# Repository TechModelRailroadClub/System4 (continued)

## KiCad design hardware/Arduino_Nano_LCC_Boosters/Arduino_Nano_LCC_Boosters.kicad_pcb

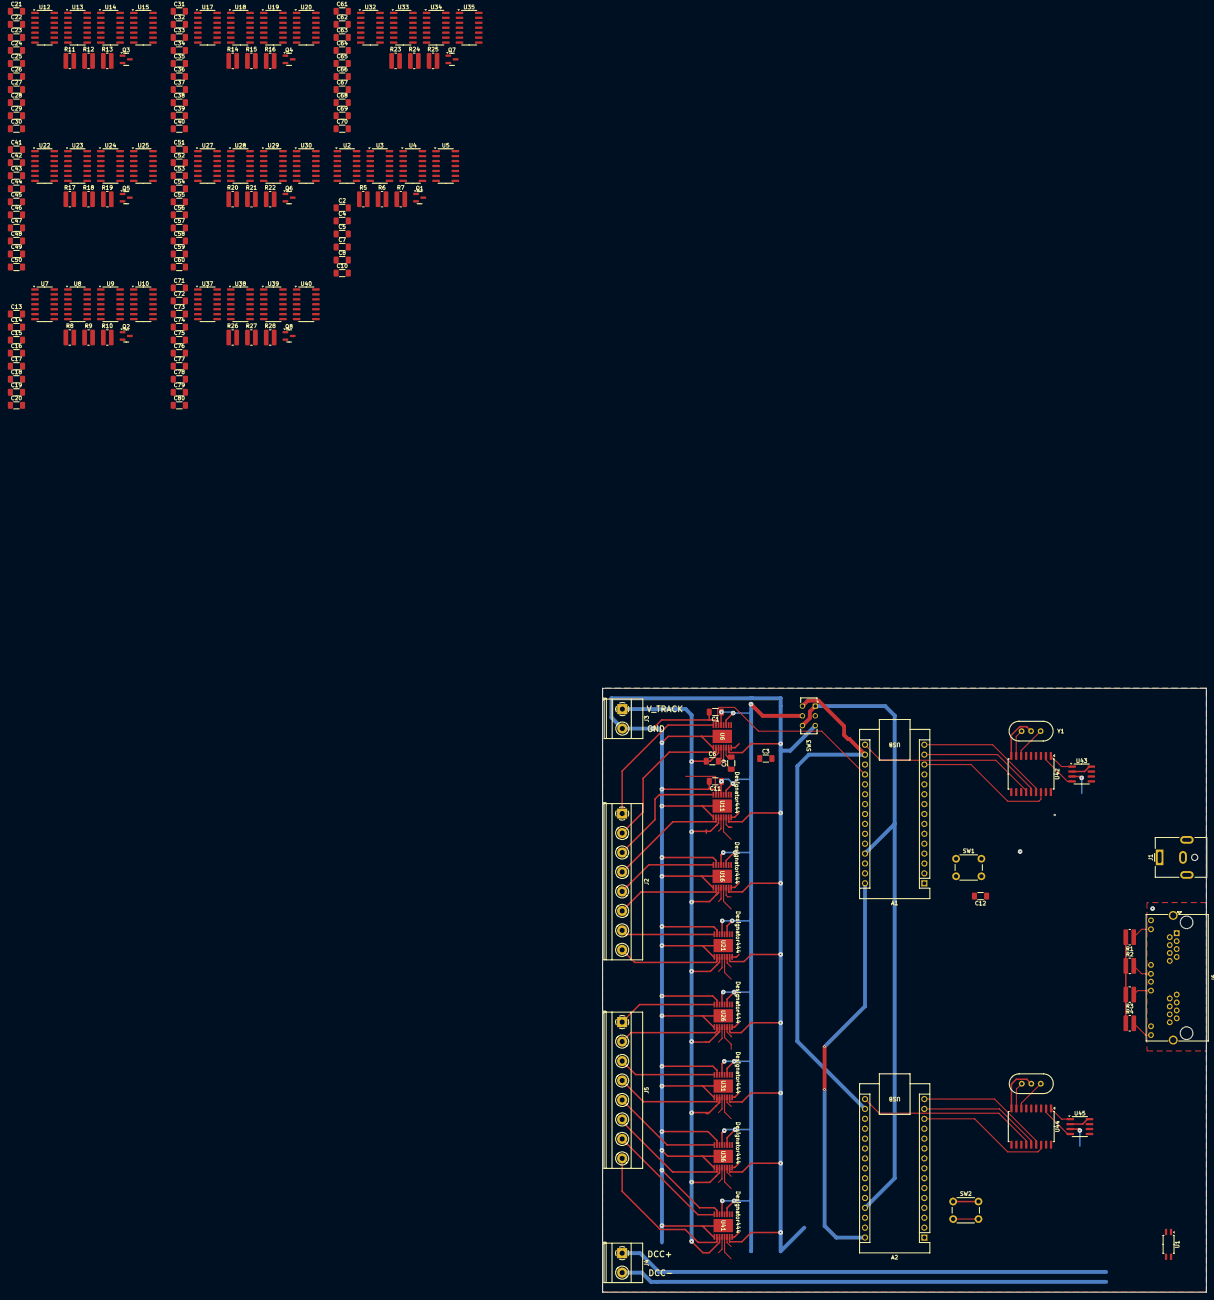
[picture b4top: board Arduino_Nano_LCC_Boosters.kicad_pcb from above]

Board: 2 copper layers, 155.0 x 155.0 mm, 174 parts (0 on the bottom side), 215 nets.

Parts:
A1, A2: Arduino_Nano_v3.x; Arduino_Nano
C1, C2, C3, C4, C5, C6, C8, C11, C12, C13, C14, C15, C16, C18, C21, C22, C23, C24, C25, C26, C28, C31, C32, C33, C34, C35, C36, C38, C41, C42, C43, C44, C45, C46, C48, C51, C52, C53, C54, C55, C56, C58, C61, C62, C63, C64, C65, C66, C68, C71, C72, C73, C74, C75, C76, C78: C100n; C_1206_3216Metric_Pad1.33x1.80mm_HandSolder
C7, C17, C27, C37, C47, C57, C67, C77: C10u; C_1206_3216Metric_Pad1.33x1.80mm_HandSolder
C9, C10, C19, C20, C29, C30, C39, C40, C49, C50, C59, C60, C69, C70, C79, C80: C22n; C_1206_3216Metric_Pad1.33x1.80mm_HandSolder
J1: Barrel_Jack_MountingPin; BarrelJack_CUI_PJ-063AH_Horizontal
J2, J5: Screw_Terminal_01x08; TerminalBlock_Phoenix_MKDS-1,5-8_1x08_P5.00mm_Horizontal
J3, J4: Screw_Terminal_01x02; TerminalBlock_Phoenix_MKDS-1,5-2_1x02_P5.00mm_Horizontal
J6: RJ45_LED_Shielded_x2; RJ45_Amphenol_RJHSE538X-02
Q1, Q2, Q3, Q4, Q5, Q6, Q7, Q8: AO3400A; SOT-23
R1, R2, R3, R4: R1k; R_0815_2038Metric_Pad1.20x4.05mm_HandSolder
R5, R8, R11, R14, R17, R20, R23, R26: R47k; R_0815_2038Metric_Pad1.20x4.05mm_HandSolder
R6, R9, R12, R15, R18, R21, R24, R27: R1k43; R_0815_2038Metric_Pad1.20x4.05mm_HandSolder
R7, R10, R13, R16, R19, R22, R25, R28: R732; R_0815_2038Metric_Pad1.20x4.05mm_HandSolder
SW1, SW2: SW_Push; SW_PUSH_6mm_H4.3mm
SW3: SW_Slide_DPDT; SW_CK_JS202011CQN_DPDT_Straight
U1: ACPL-214-500E; SOP-4_4.4x2.6mm_P1.27mm
U2, U3, U4, U5, U7, U8, U9, U10, U12, U13, U14, U15, U17, U18, U19, U20, U22, U23, U24, U25, U27, U28, U29, U30, U32, U33, U34, U35, U37, U38, U39, U40: 7410; SOIC-14_3.9x8.7mm_P1.27mm
U6, U11, U16, U21, U26, U31, U36, U41: DRV8874PWPR; PWP0016J_NV
U42, U44: MCP2515-xSO; SOIC-18W_7.5x11.6mm_P1.27mm
U43, U45: MCP2562-E-SN; SOIC-8_3.9x4.9mm_P1.27mm
Y1, Y2: 16.0 MHz, 22pF; Crystal_HC49-U-3Pin_Vertical

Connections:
3v3_IOREF: Q1.1 (G), Q2.1 (G), Q3.1 (G), Q4.1 (G), Q5.1 (G), Q6.1 (G), Q7.1 (G), Q8.1 (G), SW3.2 (B)
+3.3V: A1.17 (3V3), A2.17 (3V3), SW3.6 (C)
+5V: A1.27 (+5V), A2.27 (+5V), SW3.1 (A), SW3.4 (A), U43.3 (VDD), U45.3 (VDD)
/can_h: J6.1, J6.13, U43.7 (CANH), U45.7 (CANH)
/can_l: J6.2, J6.14, U43.6 (CANL), U45.6 (CANL)
/can_shield: J6.6, J6.18, J6.SH
/cipo_1: A1.15 (D12), U42.15 (SO)
/cipo_2: A2.15 (D12), U44.15 (SO)
/copi_1: A1.14 (D11), U42.14 (SI)
/copi_2: A2.14 (D11), U44.14 (SI)
/cs_1: A1.13 (D10), U42.16 (~CS)
/cs_2: A2.13 (D10), U44.16 (~CS)
/dcc_en_A: A1.25 (A6), U2.1, U2.2, U2.13, U3.2, U3.4, U4.2, U4.4
/dcc_en_B: A1.26 (A7), U7.1, U7.2, U7.13, U8.2, U8.4, U9.2, U9.4
/dcc_en_C: A1.2 (D0/RX), U12.1, U12.2, U12.13, U13.2, U13.4, U14.2, U14.4
/dcc_en_D: A1.1 (D1/TX), U17.1, U17.2, U17.13, U18.2, U18.4, U19.2, U19.4
/dcc_en_E: A2.25 (A6), U22.1, U22.2, U22.13, U23.2, U23.4, U24.2, U24.4
/dcc_en_F: A2.26 (A7), U27.1, U27.2, U27.13, U28.2, U28.4, U29.2, U29.4
/dcc_en_G: A2.2 (D0/RX), U32.1, U32.2, U32.13, U33.2, U33.4, U34.2, U34.4
/dcc_en_H: A2.1 (D1/TX), U37.1, U37.2, U37.13, U38.2, U38.4, U39.2, U39.4
/dcc_p: A1.11 (D8), A2.11 (D8), U1.3, U2.9, U2.10, U2.11, U3.3, U4.1, U7.9, U7.10, U7.11, U8.3, U9.1, U12.9, U12.10, U12.11, U13.3, U14.1, U17.9, U17.10, U17.11, U18.3, U19.1, U22.9, U22.10, U22.11, U23.3, U24.1, U27.9, U27.10, U27.11, U28.3, U29.1, U32.9, U32.10, U32.11, U33.3, U34.1, U37.9, U37.10, U37.11, U38.3, U39.1
/dir_A: A1.23 (A4), U2.3, U2.4, U2.5, U3.13, U4.11, U4.13
/dir_B: A1.24 (A5), U7.3, U7.4, U7.5, U8.13, U9.11, U9.13
/dir_C: A1.5 (D2), U12.3, U12.4, U12.5, U13.13, U14.11, U14.13
/dir_D: A1.7 (D4), U17.3, U17.4, U17.5, U18.13, U19.11, U19.13
/dir_E: A2.23 (A4), U22.3, U22.4, U22.5, U23.13, U24.11, U24.13
/dir_F: A2.24 (A5), U27.3, U27.4, U27.5, U28.13, U29.11, U29.13
/dir_G: A2.5 (D2), U32.3, U32.4, U32.5, U33.13, U34.11, U34.13
/dir_H: A2.7 (D4), U37.3, U37.4, U37.5, U38.13, U39.11, U39.13
/out1_A: J2.1, U6.8 (OUT1)
/out1_B: J2.3, U11.8 (OUT1)
/out1_C: J2.5, U16.8 (OUT1)
/out1_D: J2.7, U21.8 (OUT1)
/out1_E: J5.1, U26.8 (OUT1)
/out1_F: J5.3, U31.8 (OUT1)
/out1_G: J5.5, U36.8 (OUT1)
/out1_H: J5.7, U41.8 (OUT1)
/out2_A: J2.2, U6.10 (OUT2)
/out2_B: J2.4, U11.10 (OUT2)
/out2_C: J2.6, U16.10 (OUT2)
/out2_D: J2.8, U21.10 (OUT2)
/out2_E: J5.2, U26.10 (OUT2)
/out2_F: J5.4, U31.10 (OUT2)
/out2_G: J5.6, U36.10 (OUT2)
/out2_H: J5.8, U41.10 (OUT2)
/pwm_A: A1.6 (D3), U3.9, U4.9
/pwm_B: A1.12 (D9), U8.9, U9.9
/pwm_C: A1.9 (D6), U13.9, U14.9
/pwm_D: A1.8 (D5), U18.9, U19.9
/pwm_E: A2.6 (D3), U23.9, U24.9
/pwm_F: A2.12 (D9), U28.9, U29.9
/pwm_G: A2.9 (D6), U33.9, U34.9
/pwm_H: A2.8 (D5), U38.9, U39.9
/pwr_n: J6.7, J6.19
/pwr_p: J6.8, J6.20
/raw_dcc_n: J4.2, J6.4, J6.16
/raw_dcc_p: J4.1, J6.5, J6.17, U1.1
/sck_1: A1.16 (D13), U42.13 (SCK)
/sck_2: A2.16 (D13), U44.13 (SCK)
/sense_A: A1.19 (A0), C10.1, R6.1, U6.6 (IPROPI)
/sense_B: A1.20 (A1), C20.1, R9.1, U11.6 (IPROPI)
/sense_C: A1.21 (A2), C30.1, R12.1, U16.6 (IPROPI)
/sense_D: A1.22 (A3), C40.1, R15.1, U21.6 (IPROPI)
/sense_E: A2.19 (A0), C50.1, R18.1, U26.6 (IPROPI)
/sense_F: A2.20 (A1), C60.1, R21.1, U31.6 (IPROPI)
/sense_G: A2.21 (A2), C70.1, R24.1, U36.6 (IPROPI)
/sense_H: A2.22 (A3), C80.1, R27.1, U41.6 (IPROPI)
/~led_1: A1.10 (D7), J6.9, J6.21
/~led_2: A2.10 (D7), J6.11, J6.23
/~reset_1: A1.3 (~RESET), A1.28 (~RESET), SW1.2, U42.17 (~RESET)
/~reset_2: A2.3 (~RESET), A2.28 (~RESET), SW2.2, U44.17 (~RESET)
GND: A1.4 (GND), A1.29 (GND), A2.4 (GND), A2.29 (GND), C1.2, C2.2, C3.2, C4.2, C5.2, C7.2, C8.2, C10.2, C11.2, C13.2, C14.2, C15.2, C17.2, C18.2, C20.2, C21.2, C22.2, C23.2, C24.2, C25.2, C27.2, C28.2, C30.2, C31.2, C32.2, C33.2, C34.2, C35.2, C37.2, C38.2, C40.2, C41.2, C42.2, C43.2, C44.2, C45.2, C47.2, C48.2, C50.2, C51.2, C52.2, C53.2, C54.2, C55.2, C57.2, C58.2, C60.2, C61.2, C62.2, C63.2, C64.2, C65.2, C67.2, C68.2, C70.2, C71.2, C72.2, C73.2, C74.2, C75.2, C77.2, C78.2, C80.2, J1.2, J1.MP (MountPin), J3.2, J6.3, J6.15, Q1.2 (S), Q2.2 (S), Q3.2 (S), Q4.2 (S), Q5.2 (S), Q6.2 (S), Q7.2 (S), Q8.2 (S), R7.2, R10.2, R13.2, R16.2, R19.2, R22.2, R25.2, R28.2, SW1.1, SW2.1, SW3.3 (C), U1.2, U2.7 (GND), U3.7 (GND), U4.7 (GND), U5.7 (GND), U6.7 (IMODE), U6.9 (PGND), U6.15 (GND), U6.17 (PAD), U7.7 (GND), U8.7 (GND), U9.7 (GND), U10.7 (GND), U11.7 (IMODE), U11.9 (PGND), U11.15 (GND), U11.17 (PAD), U12.7 (GND), U13.7 (GND), U14.7 (GND), U15.7 (GND), U16.7 (IMODE), U16.9 (PGND), U16.15 (GND), U16.17 (PAD), U17.7 (GND), U18.7 (GND), U19.7 (GND), U20.7 (GND), U21.7 (IMODE), U21.9 (PGND), U21.15 (GND), U21.17 (PAD), U22.7 (GND), U23.7 (GND), U24.7 (GND), U25.7 (GND), U26.7 (IMODE), U26.9 (PGND), U26.15 (GND), U26.17 (PAD), U27.7 (GND), U28.7 (GND), U29.7 (GND), U30.7 (GND), U31.7 (IMODE), U31.9 (PGND), U31.15 (GND), U31.17 (PAD), U32.7 (GND), U33.7 (GND), U34.7 (GND), U35.7 (GND), U36.7 (IMODE), U36.9 (PGND), U36.15 (GND), U36.17 (PAD), U37.7 (GND), U38.7 (GND), U39.7 (GND), U40.7 (GND), U41.7 (IMODE), U41.9 (PGND), U41.15 (GND), U41.17 (PAD), U42.9 (VSS), U43.2 (VSS), U43.8 (STBY), U44.9 (VSS), U45.2 (VSS), U45.8 (STBY), Y1.2, Y2.2
IOREF: C1.1, C2.1, C3.1, C4.1, C5.1, C11.1, C13.1, C14.1, C15.1, C21.1, C22.1, C23.1, C24.1, C25.1, C31.1, C32.1, C33.1, C34.1, C35.1, C41.1, C42.1, C43.1, C44.1, C45.1, C51.1, C52.1, C53.1, C54.1, C55.1, C61.1, C62.1, C63.1, C64.1, C65.1, C71.1, C72.1, C73.1, C74.1, C75.1, R1.2, R2.1, R3.2, R4.1, R5.1, R8.1, R11.1, R14.1, R17.1, R20.1, R23.1, R26.1, SW3.5 (B), U1.4, U2.14 (VCC), U3.14 (VCC), U4.14 (VCC), U5.14 (VCC), U6.3 (SLEEP_N), U6.5 (VREF), U6.16 (PMODE), U7.14 (VCC), U8.14 (VCC), U9.14 (VCC), U10.14 (VCC), U11.3 (SLEEP_N), U11.5 (VREF), U11.16 (PMODE), U12.14 (VCC), U13.14 (VCC), U14.14 (VCC), U15.14 (VCC), U16.3 (SLEEP_N), U16.5 (VREF), U16.16 (PMODE), U17.14 (VCC), U18.14 (VCC), U19.14 (VCC), U20.14 (VCC), U21.3 (SLEEP_N), U21.5 (VREF), U21.16 (PMODE), U22.14 (VCC), U23.14 (VCC), U24.14 (VCC), U25.14 (VCC), U26.3 (SLEEP_N), U26.5 (VREF), U26.16 (PMODE), U27.14 (VCC), U28.14 (VCC), U29.14 (VCC), U30.14 (VCC), U31.3 (SLEEP_N), U31.5 (VREF), U31.16 (PMODE), U32.14 (VCC), U33.14 (VCC), U34.14 (VCC), U35.14 (VCC), U36.3 (SLEEP_N), U36.5 (VREF), U36.16 (PMODE), U37.14 (VCC), U38.14 (VCC), U39.14 (VCC), U40.14 (VCC), U41.3 (SLEEP_N), U41.5 (VREF), U41.16 (PMODE), U42.18 (VDD), U43.5 (Vio), U44.18 (VDD), U45.5 (Vio)
unnamed: J6.10, R1.1
unnamed: J6.12, R2.2
unnamed: J6.22, R3.1
unnamed: J6.24, R4.2
unnamed: Q1.3 (D), R6.2, R7.1
unnamed: Q2.3 (D), R9.2, R10.1
unnamed: Q3.3 (D), R12.2, R13.1
unnamed: Q4.3 (D), R15.2, R16.1
unnamed: Q5.3 (D), R18.2, R19.1
unnamed: Q6.3 (D), R21.2, R22.1
unnamed: Q7.3 (D), R24.2, R25.1
unnamed: Q8.3 (D), R27.2, R28.1
unnamed: U2.6, U3.5, U3.11, U4.5
unnamed: U2.8, U3.1, U4.3
unnamed: U2.12, U3.10, U4.10
unnamed: U3.6, U5.2
unnamed: U3.8, U5.13
unnamed: U3.12, U5.1
unnamed: U4.6, U5.4
unnamed: U4.8, U5.5
unnamed: U4.12, U5.3
unnamed: C9.1, U6.13 (CPH)
unnamed: C9.2, U6.14 (CPL)
unnamed: U5.12, U6.1 (EN_IN1)
unnamed: R5.2, U6.4 (FAULT_N)
unnamed: U5.6, U6.2 (PH_IN2)
unnamed: C6.2, U6.12 (VCP)
unnamed: U7.6, U8.5, U8.11, U9.5
unnamed: U7.8, U8.1, U9.3
unnamed: U7.12, U8.10, U9.10
unnamed: U8.12, U10.1
unnamed: U8.6, U10.2
unnamed: U9.12, U10.3
unnamed: U9.6, U10.4
unnamed: U9.8, U10.5
unnamed: U8.8, U10.13
unnamed: C19.1, U11.13 (CPH)
unnamed: C19.2, U11.14 (CPL)
unnamed: U10.12, U11.1 (EN_IN1)
unnamed: R8.2, U11.4 (FAULT_N)
unnamed: U10.6, U11.2 (PH_IN2)
unnamed: C16.2, U11.12 (VCP)
unnamed: U12.6, U13.5, U13.11, U14.5
unnamed: U12.8, U13.1, U14.3
unnamed: U12.12, U13.10, U14.10
unnamed: U13.6, U15.2
unnamed: U13.8, U15.13
unnamed: U13.12, U15.1
unnamed: U14.6, U15.4
unnamed: U14.8, U15.5
unnamed: U14.12, U15.3
unnamed: C29.1, U16.13 (CPH)
unnamed: C29.2, U16.14 (CPL)
unnamed: U15.12, U16.1 (EN_IN1)
unnamed: R11.2, U16.4 (FAULT_N)
unnamed: U15.6, U16.2 (PH_IN2)
unnamed: C26.2, U16.12 (VCP)
unnamed: U17.6, U18.5, U18.11, U19.5
unnamed: U17.8, U18.1, U19.3
unnamed: U17.12, U18.10, U19.10
unnamed: U18.6, U20.2
unnamed: U18.8, U20.13
unnamed: U18.12, U20.1
unnamed: U19.6, U20.4
unnamed: U19.8, U20.5
unnamed: U19.12, U20.3
unnamed: C39.1, U21.13 (CPH)
unnamed: C39.2, U21.14 (CPL)
unnamed: U20.12, U21.1 (EN_IN1)
unnamed: R14.2, U21.4 (FAULT_N)
unnamed: U20.6, U21.2 (PH_IN2)
unnamed: C36.2, U21.12 (VCP)
unnamed: U22.6, U23.5, U23.11, U24.5
unnamed: U22.8, U23.1, U24.3
unnamed: U22.12, U23.10, U24.10
unnamed: U23.6, U25.2
unnamed: U23.8, U25.13
unnamed: U23.12, U25.1
unnamed: U24.6, U25.4
unnamed: U24.8, U25.5
unnamed: U24.12, U25.3
unnamed: C49.1, U26.13 (CPH)
unnamed: C49.2, U26.14 (CPL)
unnamed: U25.12, U26.1 (EN_IN1)
unnamed: R17.2, U26.4 (FAULT_N)
unnamed: U25.6, U26.2 (PH_IN2)
unnamed: C46.2, U26.12 (VCP)
unnamed: U27.6, U28.5, U28.11, U29.5
unnamed: U27.8, U28.1, U29.3
unnamed: U27.12, U28.10, U29.10
unnamed: U28.6, U30.2
unnamed: U28.8, U30.13
unnamed: U28.12, U30.1
unnamed: U29.6, U30.4
unnamed: U29.8, U30.5
unnamed: U29.12, U30.3
unnamed: C59.1, U31.13 (CPH)
unnamed: C59.2, U31.14 (CPL)
unnamed: U30.12, U31.1 (EN_IN1)
unnamed: R20.2, U31.4 (FAULT_N)
unnamed: U30.6, U31.2 (PH_IN2)
unnamed: C56.2, U31.12 (VCP)
unnamed: U32.6, U33.5, U33.11, U34.5
unnamed: U32.8, U33.1, U34.3
unnamed: U32.12, U33.10, U34.10
unnamed: U33.6, U35.2
unnamed: U33.8, U35.13
unnamed: U33.12, U35.1
unnamed: U34.6, U35.4
unnamed: U34.8, U35.5
unnamed: U34.12, U35.3
unnamed: C69.1, U36.13 (CPH)
unnamed: C69.2, U36.14 (CPL)
unnamed: U35.12, U36.1 (EN_IN1)
unnamed: R23.2, U36.4 (FAULT_N)
unnamed: U35.6, U36.2 (PH_IN2)
unnamed: C66.2, U36.12 (VCP)
unnamed: U37.6, U38.5, U38.11, U39.5
unnamed: U37.8, U38.1, U39.3
unnamed: U37.12, U38.10, U39.10
unnamed: U38.6, U40.2
unnamed: U38.8, U40.13
unnamed: U38.12, U40.1
unnamed: U39.6, U40.4
unnamed: U39.8, U40.5
unnamed: U39.12, U40.3
unnamed: C79.1, U41.13 (CPH)
unnamed: C79.2, U41.14 (CPL)
unnamed: U40.12, U41.1 (EN_IN1)
unnamed: R26.2, U41.4 (FAULT_N)
unnamed: U40.6, U41.2 (PH_IN2)
unnamed: C76.2, U41.12 (VCP)
unnamed: U42.8 (OSC1), Y1.3
unnamed: U42.7 (OSC2), Y1.1
unnamed: U42.2 (RXCAN), U43.4 (RXD)
unnamed: U42.1 (TXCAN), U43.1 (TXD)
unnamed: U44.8 (OSC1), Y2.3
unnamed: U44.7 (OSC2), Y2.1
unnamed: U44.2 (RXCAN), U45.4 (RXD)
unnamed: U44.1 (TXCAN), U45.1 (TXD)
VIN: A1.30 (VIN), A2.30 (VIN), J1.1
VTRACK: C6.1, C7.1, C8.1, C16.1, C17.1, C18.1, C26.1, C27.1, C28.1, C36.1, C37.1, C38.1, C46.1, C47.1, C48.1, C56.1, C57.1, C58.1, C66.1, C67.1, C68.1, C76.1, C77.1, C78.1, J3.1, U6.11 (VM), U11.11 (VM), U16.11 (VM), U21.11 (VM), U26.11 (VM), U31.11 (VM), U36.11 (VM), U41.11 (VM)

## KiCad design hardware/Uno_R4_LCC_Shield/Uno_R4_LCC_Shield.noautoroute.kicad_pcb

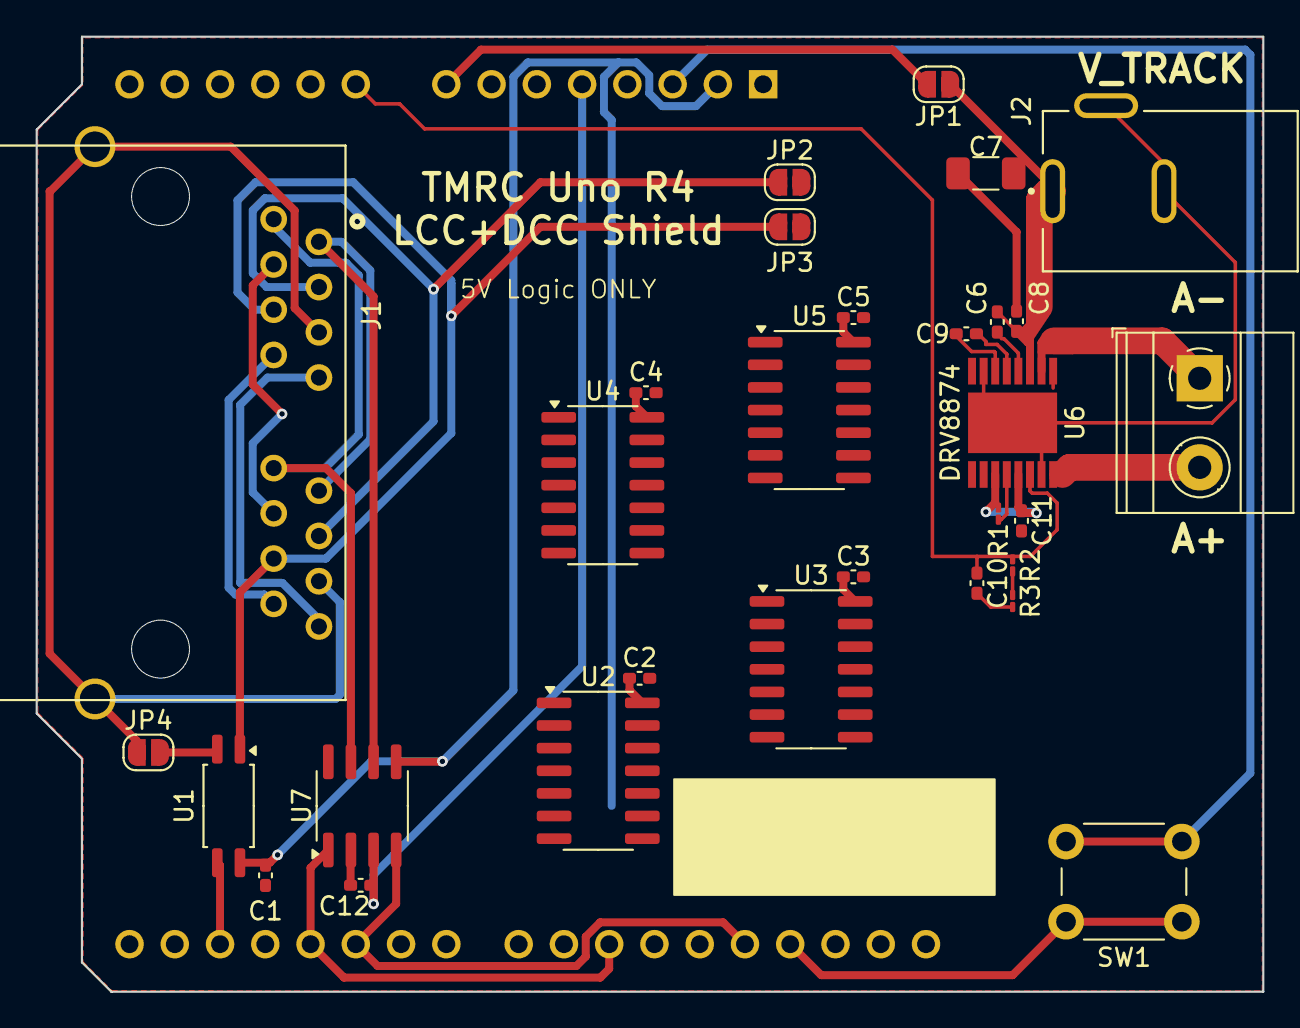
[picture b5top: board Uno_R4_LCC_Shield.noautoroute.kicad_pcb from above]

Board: 2 copper layers, 68.8 x 53.6 mm, 31 parts (1 on the bottom side), 38 nets.

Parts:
A1: Arduino_UNO_R4; Arduino_UNO_R3
C1, C2, C3, C4, C5, C6, C8, C11, C12: C100n; C_0402_1005Metric_Pad0.74x0.62mm_HandSolder
C7: C10u; C_1206_3216Metric_Pad1.33x1.80mm_HandSolder
C9, C10: C22n; C_0402_1005Metric_Pad0.74x0.62mm_HandSolder
J1: A00-216-262-450; EDAC_A00-216-262-450
J2: 54-00166; TENSILITY_54-00166
J3: Screw_Terminal_01x02; TerminalBlock_Phoenix_MKDS-1,5-2_1x02_P5.00mm_Horizontal
JP1, JP2, JP3, JP4: SolderJumper_2_Open; SolderJumper-2_P1.3mm_Open_RoundedPad1.0x1.5mm
R1: R47k; R_01005_0402Metric_Pad0.57x0.30mm_HandSolder
R2: R1k43; R_01005_0402Metric_Pad0.57x0.30mm_HandSolder
R3: R732; R_01005_0402Metric_Pad0.57x0.30mm_HandSolder
SW1: SW_Push; SW_PUSH_6mm_H4.3mm
U1: ACPL-214-500E; SOP-4_4.4x2.6mm_P1.27mm
U2, U3, U4, U5: 7410; SOIC-14_3.9x8.7mm_P1.27mm
U6: DRV8874PWPR; PWP0016J_NV
U7: MCP2562-E-SN; SOIC-8_3.9x4.9mm_P1.27mm

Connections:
+5V: A1.5 (+5V), C12.1, U7.3 (VDD)
/can_h: J1.1, J1.9 (1), U7.7 (CANH)
/can_l: J1.2, J1.10 (2), U7.6 (CANL)
/can_rx: A1.20 (D5), A1.28 (D13), U7.4 (RXD)
/can_shield: J1.6, J1.14 (6), J1.M1 (SHIELD), J1.M2 (SHIELD), JP4.1 (A)
/can_tx: A1.19 (D4), A1.25 (D10), U7.1 (TXD)
/dcc_en_A: A1.22 (D7), U2.1, U2.2, U2.13, U3.2, U3.4, U4.2, U4.4
/dcc_p: A1.17 (D2), U1.3, U2.9, U2.10, U2.11, U3.3, U4.1
/dir_A: A1.21 (D6), U2.3, U2.4, U2.5, U3.13, U4.11, U4.13
/out1_A: J3.2, JP3.2 (B), U6.8 (OUT1)
/out2_A: J3.1, JP2.2 (B), U6.10 (OUT2)
/pwm_A: A1.18 (D3), U3.9, U4.9
/pwr_n: J1.7, J1.15 (7)
/pwr_p: J1.8, J1.16 (8)
/raw_dcc_n: J1.4, J1.12 (4), JP2.1 (A)
/raw_dcc_p: J1.5, J1.13 (5), JP3.1 (A), U1.1
/sense_A: A1.9 (A0), C10.1, R2.1, U6.6 (IPROPI)
/~reset: A1.3 (~RESET), SW1.2
GND: A1.6 (GND), A1.7 (GND), A1.29 (GND), C1.2, C2.2, C3.2, C4.2, C5.2, C7.2, C8.2, C10.2, C11.2, C12.2, J1.3, J1.11 (3), J2.B, J2.C, JP4.2 (B), R3.2, SW1.1, U1.2, U2.7 (GND), U3.7 (GND), U4.7 (GND), U5.7 (GND), U6.7 (IMODE), U6.9 (PGND), U6.15 (GND), U6.17 (PAD), U7.2 (VSS), U7.8 (STBY)
IOREF: A1.2 (IOREF), C1.1, C2.1, C3.1, C4.1, C5.1, C11.1, R1.1, U1.4, U2.14 (VCC), U3.14 (VCC), U4.14 (VCC), U5.14 (VCC), U6.3 (SLEEP_N), U6.5 (VREF), U6.16 (PMODE), U7.5 (Vio)
unnamed: R2.2, R3.1
unnamed: U2.6, U3.5, U3.11, U4.5
unnamed: U2.8, U3.1, U4.3
unnamed: U2.12, U3.10, U4.10
unnamed: U3.6, U5.2
unnamed: U3.8, U5.13
unnamed: U3.12, U5.1
unnamed: U4.6, U5.4
unnamed: U4.8, U5.5
unnamed: U4.12, U5.3
unnamed: C9.1, U6.13 (CPH)
unnamed: C9.2, U6.14 (CPL)
unnamed: U5.12, U6.1 (EN_IN1)
unnamed: R1.2, U6.4 (FAULT_N)
unnamed: U5.6, U6.2 (PH_IN2)
unnamed: C6.2, U6.12 (VCP)
VIN: A1.8 (VIN), JP1.2 (B)
VTRACK: C6.1, C7.1, C8.1, J2.A, JP1.1 (A), U6.11 (VM)

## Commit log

2024-03-22 Add Board Project
2024-03-24 Board complete except power
2024-03-26 Made double nano board and updated CAN, added temporary power solution
2024-03-26 Create LICENSE
2024-03-27 Started placement and routing
2024-04-14 Switch to single Arduino per board
2024-04-14 Shrunk and added standoffs
2024-04-14 Remove KiCad lock
2024-04-16 Small Tweaks
2024-04-17 Fixed some footprints
2024-04-28 LCC Booster v1.0
2024-04-28 LCC Command Station Shield
2024-04-28 Regenerate LCC Booster Gerbers
2024-04-29 Regenerate LCC Booster Gerbers with More Power Filtering
2024-05-03 Start to work on code structure and added MCP2515 interrupt
2024-05-03 Added MCP2515 Interrupt capability
2024-05-09 Better Solder Jumpers, Better Pizza
2024-05-09 Don't forget to zip up!
2024-05-15 Update to hardware v2 and cleanup
2024-05-16 Small tweaks to pinout on Uno R4 Shield and additional cleanup
2024-08-08 Reconfiguration
2024-08-25 Reorganize arduino source
2024-09-06 Update Schematic
2024-09-10 Add Fault Pin Inputs to Arduino
2024-09-14 Fix Some Hardware Pin Notations
2024-10-17 Add Block Functionality
2024-10-25 Setup system4dispatch and Add Layout Ingestion Functionality
2024-10-25 Add JSON graph map
2024-11-13 Update for PCB Assembly
2024-11-16 Version 5 of PCB
2024-12-06 Added location holes to solder paste template
2025-01-09 Add Pico Card
2025-01-21 PicoLCC
2025-07-22 Update LCC Booster
